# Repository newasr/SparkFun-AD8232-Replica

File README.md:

# AD8232-PCB-Design
KiCad v9 PCB design replicating the SparkFun AD8232 ECG module

## 1. Overview  
This project is a **replica** of the [SparkFun AD8232 ECG module](https://www.digikey.in/en/products/detail/sparkfun-electronics/SEN-12650/5824153) designed using **KiCad v9**. It includes the schematic, PCB layout, 3D rendering, Gerber files, and BOM.  

## 2. Project Files  
- **KiCad Project Files** → Includes the schematic, PCB layout, and component libraries.  
- **Gerber Files** → Generated using the **"Gerber to Order"** plugin for PCB fabrication.  
- **Bill of Materials (BOM)** → Created using the **"Interactive HTML BOM"** plugin, with Digikey part numbers and URLs.  
- **Project Documentation (PDF)** → Contains:  
  1. **Schematic Diagram**  
  2. **PCB Layout with Dimensions**  
  3. **3D Render of the Board**  
  4. **Bill of Materials (BOM)**  

## 3. Preview

### Schematic

### PCB Layout

### 3D View

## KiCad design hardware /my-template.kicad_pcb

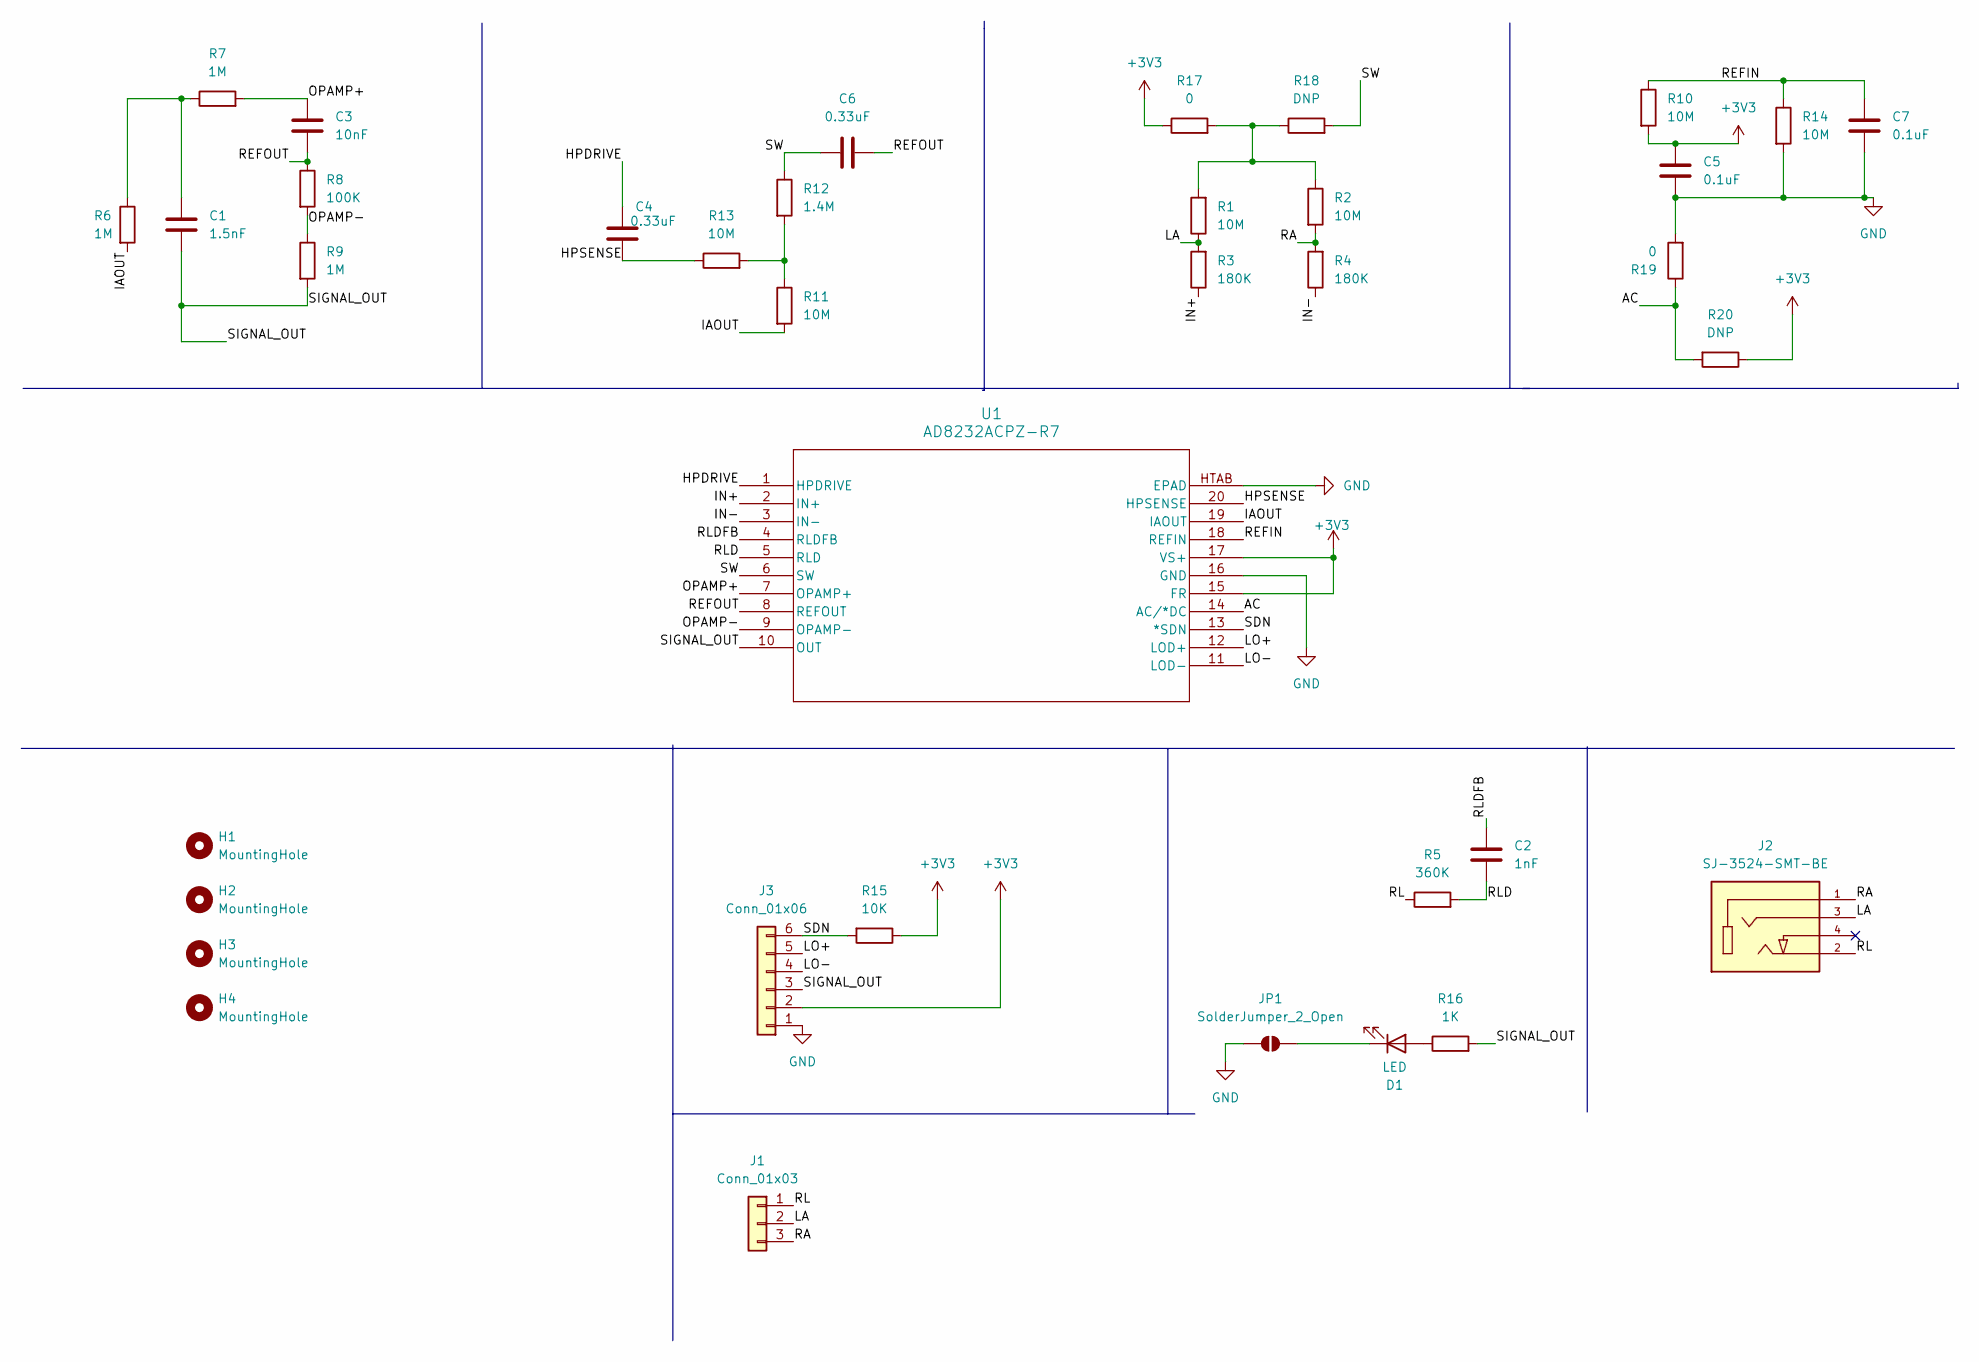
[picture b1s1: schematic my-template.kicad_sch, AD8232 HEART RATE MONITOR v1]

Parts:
C1: 1.5nF; C_0603_1608Metric; Digikey Part# 490-1455-2-ND
C2: 1nF; C_0603_1608Metric; Digikey Part# 399-C0603C102K5RACTUTR-ND
C3: 10nF; C_0603_1608Metric; Digikey Part# 1276-1009-2-ND
C4, C6: 0.33uF; C_0805_2012Metric; Digikey Part# 490-6050-2-ND
C5, C7: 0.1uF; C_0603_1608Metric; Digikey Part# 311-1088-2-ND
D1: LED; LED_0603_1608Metric; Digikey Part# 732-12017-2-ND
H1, H2, H3, H4: MountingHole; hole
J1: Conn_01x03; 3_conn
J2: SJ-3524-SMT-BE; CUI_SJ-3524-SMT-BE; Digikey Part# CP-3524SJBETR-ND
J3: Conn_01x06; 6_conn
JP1: SolderJumper_2_Open; SolderJumper-2_P1.3mm_Bridged_Pad1.0x1.5mm
R1, R2, R10, R11, R13, R14: 10M; R_0603_1608Metric; Digikey Part# 311-10MGRTR-ND
R3, R4: 180K; R_0603_1608Metric; Digikey Part# 311-180KGRTR-ND
R5: 360K; R_0603_1608Metric; Digikey Part# 311-360KHRTR-ND
R6, R7, R9: 1M; R_0603_1608Metric; Digikey Part# YAG4498TR-ND
R8: 100K; R_0603_1608Metric; Digikey Part# P100KHTR-ND
R12: 1.4M; R_0603_1608Metric; Digikey Part# RMCF0603FT1M40TR-ND
R15: 10K; R_0603_1608Metric; Digikey Part# 2019-RK73H1JTTD1002FTR-ND
R16: 1K; R_0603_1608Metric; Digikey Part# 311-1.00KHRTR-ND
R17, R19: 0; R_0603_1608Metric; Digikey Part# RMCF0603ZT0R00TR-ND
R18, R20: DNP; R_0603_1608Metric
U1: AD8232ACPZ-R7; ad8232; Digikey Part# AD8232ACPZ-R7

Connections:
+3V3: C5.1, J3.2, R10.2, R15.1, R17.1, R20.1, U1.15 (FR), U1.17 (VS+)
/AC: R19.1, R20.2, U1.14 (AC/*DC)
/HPDRIVE: C4.1, U1.1 (HPDRIVE)
/HPSENSE: C4.2, R13.1, U1.20 (HPSENSE)
/IAOUT: R6.2, R11.2, U1.19 (IAOUT)
/IN+: R3.1, U1.2 (IN+)
/IN-: R4.1, U1.3 (IN-)
/LA: J1.2, J2.3, R1.1, R3.2
/LO+: J3.5, U1.12 (LOD+)
/LO-: J3.4, U1.11 (LOD-)
/OPAMP+: C3.1, R7.2, U1.7 (OPAMP+)
/OPAMP-: R8.2, R9.1, U1.9 (OPAMP-)
/RA: J1.3, J2.1, R2.2, R4.2
/REFIN: C7.1, R10.1, R14.1, U1.18 (REFIN)
/REFOUT: C3.2, C6.2, R8.1, U1.8 (REFOUT)
/RL: J1.1, J2.2, R5.1
/RLD: C2.2, R5.2, U1.5 (RLD)
/RLDFB: C2.1, U1.4 (RLDFB)
/SDN: J3.6, R15.2, U1.13 (*SDN)
/SIGNAL_OUT: C1.2, J3.3, R9.2, R16.2, U1.10 (OUT)
/SW: C6.1, R12.1, R18.2, U1.6 (SW)
GND: C5.2, C7.2, J3.1, JP1.1 (A), R14.2, R19.2, U1.16 (GND), U1.HTAB (EPAD)
unnamed: C1.1, R6.1, R7.1
unnamed: D1.2 (A), R16.1
unnamed: D1.1 (K), JP1.2 (B)
unnamed: R1.2, R2.1, R17.2, R18.1
unnamed: R11.1, R12.2, R13.2

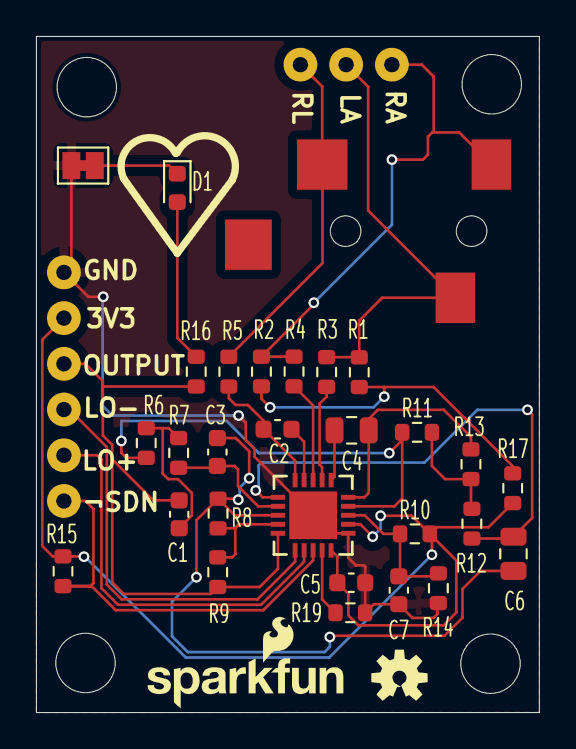
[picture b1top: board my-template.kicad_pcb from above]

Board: 2 copper layers, 27.9 x 37.6 mm, 35 parts (0 on the bottom side), 27 nets.

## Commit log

2025-03-23 added assets and updated readme
2025-03-23 added hardware files, gerber and bom
